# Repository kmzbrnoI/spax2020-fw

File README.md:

# SPAX 2020

[SPAX](http://fremodcc.sourceforge.net/booster/spaxbooster/index.html)
is a model-railroad DCC signal booster. It is a [well-known hardware
construction from FREMO model railroaders club in
Germany](http://fremodcc.sourceforge.net/booster/spaxbooster/index.html).
This repository contains firmware and PCB design for a new
processor PIC12F629 which is supposed to replace original PIC12F508 SPAX v2
processor **without** changing whole SPAX pcb.

This is a low-cost solution for eliminating old-processor disadvantages.
For future expansion (RailCom etc.) whole new SPAX should be designed.

## Why to change processor?

1. **Weird shortcut detection**
   The old processor measured current as analog signal on digital CPU input.
   This caused bad detection sometimes. The new processor reads analog input
   and uses internal comparator.

2. **Short shortcut-restore time**
   The old processor indicated shortcut when e. g. cars with larger capacitors
   were put on a track. When new processor detects shortcut, it leaves max
   current for a longer time – 20 ms. This is enough time for capacitors to
   charge.

## How to change processor in SPAX

Manufacture `12F629.brd` PCB and replace DIL8 old processor with SMD new
processor on the board.

## Firmware functionality description

Track power supply is restored after 200 ms, 400 ms, 800 ms, 1200 ms, 1200 ms,
...  after overcurrent is detected. This is long-enough time for SPAX cooler to
cool-down stabilizer and H-bridge.

H-bridge ensures that shortcut current will never be more than 3 A.

First 3 tests for overcurrent-restore allow only 5 ms of max current, all next
tests allow max current for 20 ms.

## LEDs

* Red LED = not generating DCC on output
* Green LED = DCC on input

States:

* Green: generating DCC to track
* Red: DCC on input present, but shortcut detected
* Yellow: DCC not on input

## Authors

 * hardware: Jan Horacek
 * firmware: Michal Petrilak, Jan Horacek

## License

The firmware and PCB design is distributed as opensource project under
Apache License v2.0.

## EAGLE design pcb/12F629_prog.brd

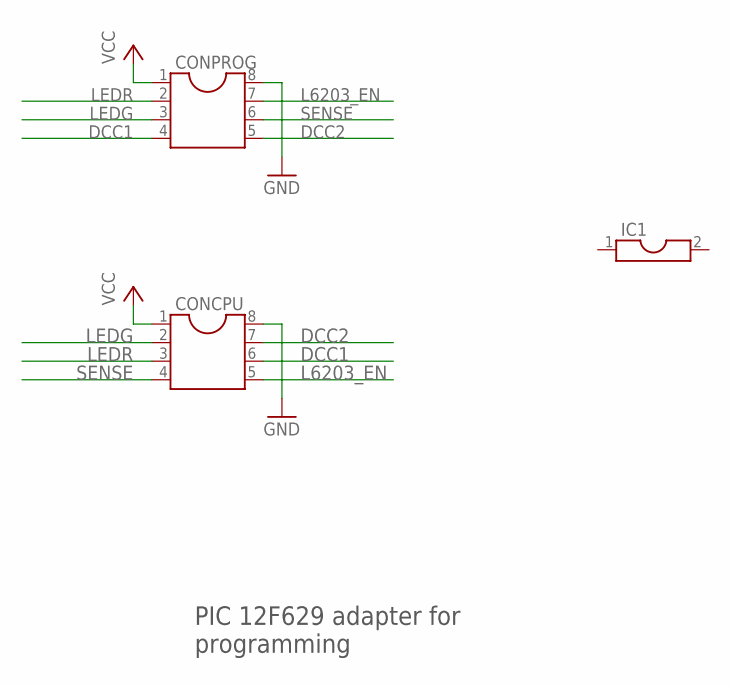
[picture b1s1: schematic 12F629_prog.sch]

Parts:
CONCPU: DIL8; DIL08
CONPROG: DIL8; DIL08
IC1: DIL2; DIL02

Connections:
DCC1: CONCPU.6, CONPROG.4
DCC2: CONCPU.7, CONPROG.5
GND: CONCPU.8, CONPROG.8
L6203_EN: CONCPU.5, CONPROG.7
LEDG: CONCPU.2, CONPROG.3
LEDR: CONCPU.3, CONPROG.2
SENSE: CONCPU.4, CONPROG.6
VCC: CONCPU.1, CONPROG.1

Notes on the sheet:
PIC 12F629 adapter for programming

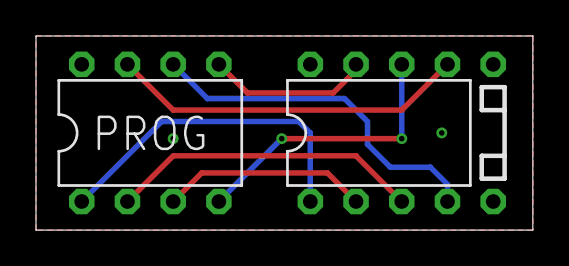
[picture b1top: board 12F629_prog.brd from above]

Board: 2 copper layers, 27.6 x 10.8 mm, 3 parts (0 on the bottom side), 8 nets.

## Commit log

2020-09-15 first working version
2020-09-15 Add .gitignore.
2020-09-15 Add real author to LICENSE.
2020-09-16 Move firmware to special directory.
2020-09-16 Add PCB.
2020-09-16 Add README.
2020-09-18 Update contributors.
2020-09-20 Add link to FREMO SPAX
2020-09-20 FIx typos.
2020-09-27 Overcurrent is detected with delay.
    4 successiver eadings each at 250 ns (1 us total) must read 1 to
    set overcurrent flag.
2020-09-28 Add overcurrent-stop debounce.
    This debounce is 1 us, but should be 10 us. TODO change via loop
    in future.
2020-09-28 Tweak overcurrent debouncing.
2021-05-11 Add proper deboucing for overload detection pin.
    Read pin 8 times (each 2 us), consider short-circuit when >2 reads
    indicate short-circuit.
2021-05-12 Remove unused interrupt.
2021-05-12 Remove ununsed LED blinking.
2021-05-12 Enhance Makefile.
2021-05-12 Add fuses config file.
2021-05-12 Makefile: add prg target.
2021-05-12 Remove commented-out code.
2021-05-12 Rename all variables to english.
2021-05-12 Add overload detection to separate function.
2021-05-12 Use english for constant names.
2021-05-12 Enable timer 0 @ 500 us.
2021-05-12 Name bits in english.
2021-05-12 Align comments.
2021-05-12 Calculate overload in timer.
2021-05-12 Caclulate fover based on long-term overload state.
2021-05-12 Name states in english.
2021-05-12 Add overload hystheresis.
2021-05-12 Update README.
2024-08-02 fuses.conf for new minipro v0.7.
